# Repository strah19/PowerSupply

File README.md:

# Power Supply

Basic controllable voltage power supply designed for a Eurorack. It includes a positive and negative voltage rail with an AC input.

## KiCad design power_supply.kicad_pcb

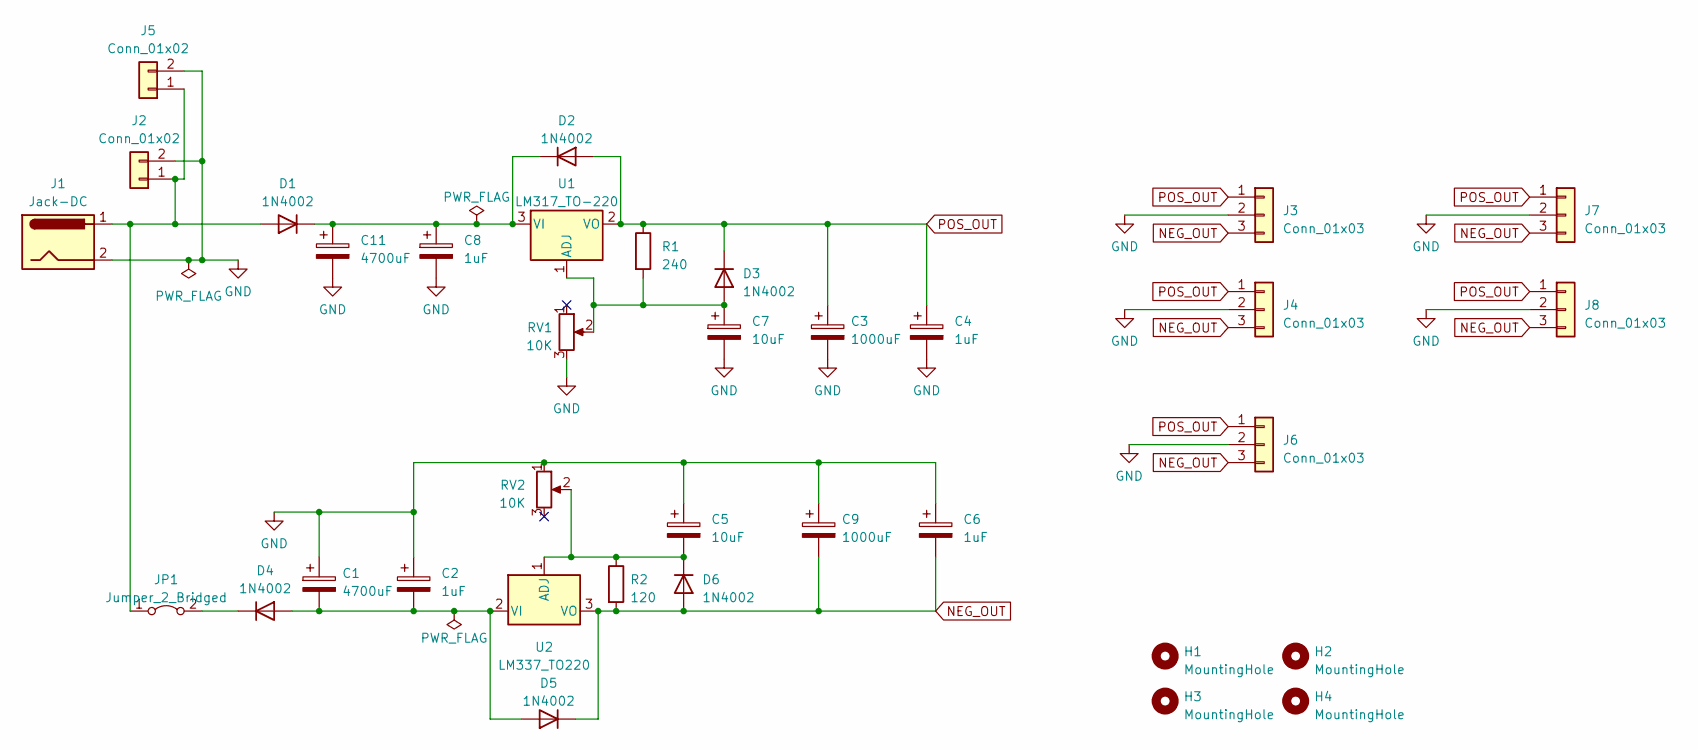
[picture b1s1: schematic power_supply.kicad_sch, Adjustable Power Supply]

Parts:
C1, C11: 4700uF; CP_Radial_D18.0mm_P7.50mm
C2, C4, C6, C8: 1uF; CP_Radial_D5.0mm_P2.50mm
C3, C9: 1000uF; CP_Radial_D13.0mm_P7.50mm
C5, C7: 10uF; CP_Radial_D5.0mm_P2.50mm
D1, D2, D3, D4, D5, D6: 1N4002; D_A-405_P7.62mm_Horizontal
H1, H2, H3, H4: MountingHole; MountingHole_3.2mm_M3_DIN965_Pad
J1: Jack-DC; BarrelJack_Horizontal
J2: Conn_01x02; PinHeader_1x02_P2.54mm_Vertical
J3, J4, J7, J8: Conn_01x03; PinHeader_1x03_P2.54mm_Vertical
J5: Conn_01x02; TerminalBlock_bornier-2_P5.08mm
J6: Conn_01x03; TerminalBlock_bornier-3_P5.08mm
JP1: Jumper_2_Bridged; PinHeader_1x02_P2.54mm_Vertical
R1: 240; R_Axial_DIN0207_L6.3mm_D2.5mm_P10.16mm_Horizontal
R2: 120; R_Axial_DIN0207_L6.3mm_D2.5mm_P10.16mm_Horizontal
RV1, RV2: 10K; Potentiometer_Bourns_3296W_Vertical
U1: LM317_TO-220; TO-220-3_Vertical
U2: LM337_TO220; TO-220-3_Vertical

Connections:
GND: C1.1, C2.1, C3.2, C4.2, C5.1, C6.1, C7.2, C8.2, C9.1, C11.2, J1.2, J2.2, J3.2, J4.2, J5.2, J6.2, J7.2, J8.2, RV1.3, RV2.1
NEG_OUT: C6.2, C9.2, D5.1 (K), D6.2 (A), J3.3, J4.3, J6.3, J7.3, J8.3, R2.2, U2.3 (VO)
unnamed: D1.2 (A), J1.1, J2.1, J5.1, JP1.1 (A)
unnamed: C8.1, C11.1, D1.1 (K), D2.1 (K), U1.3 (VI)
unnamed: C7.1, D3.2 (A), R1.2, RV1.2, U1.1 (ADJ)
unnamed: C1.2, C2.2, D4.2 (A), D5.2 (A), U2.2 (VI)
unnamed: D4.1 (K), JP1.2 (B)
unnamed: C5.2, D6.1 (K), R2.1, RV2.2, U2.1 (ADJ)
POS_OUT: C3.1, C4.1, D2.2 (A), D3.1 (K), J3.1, J4.1, J6.1, J7.1, J8.1, R1.1, U1.2 (VO)

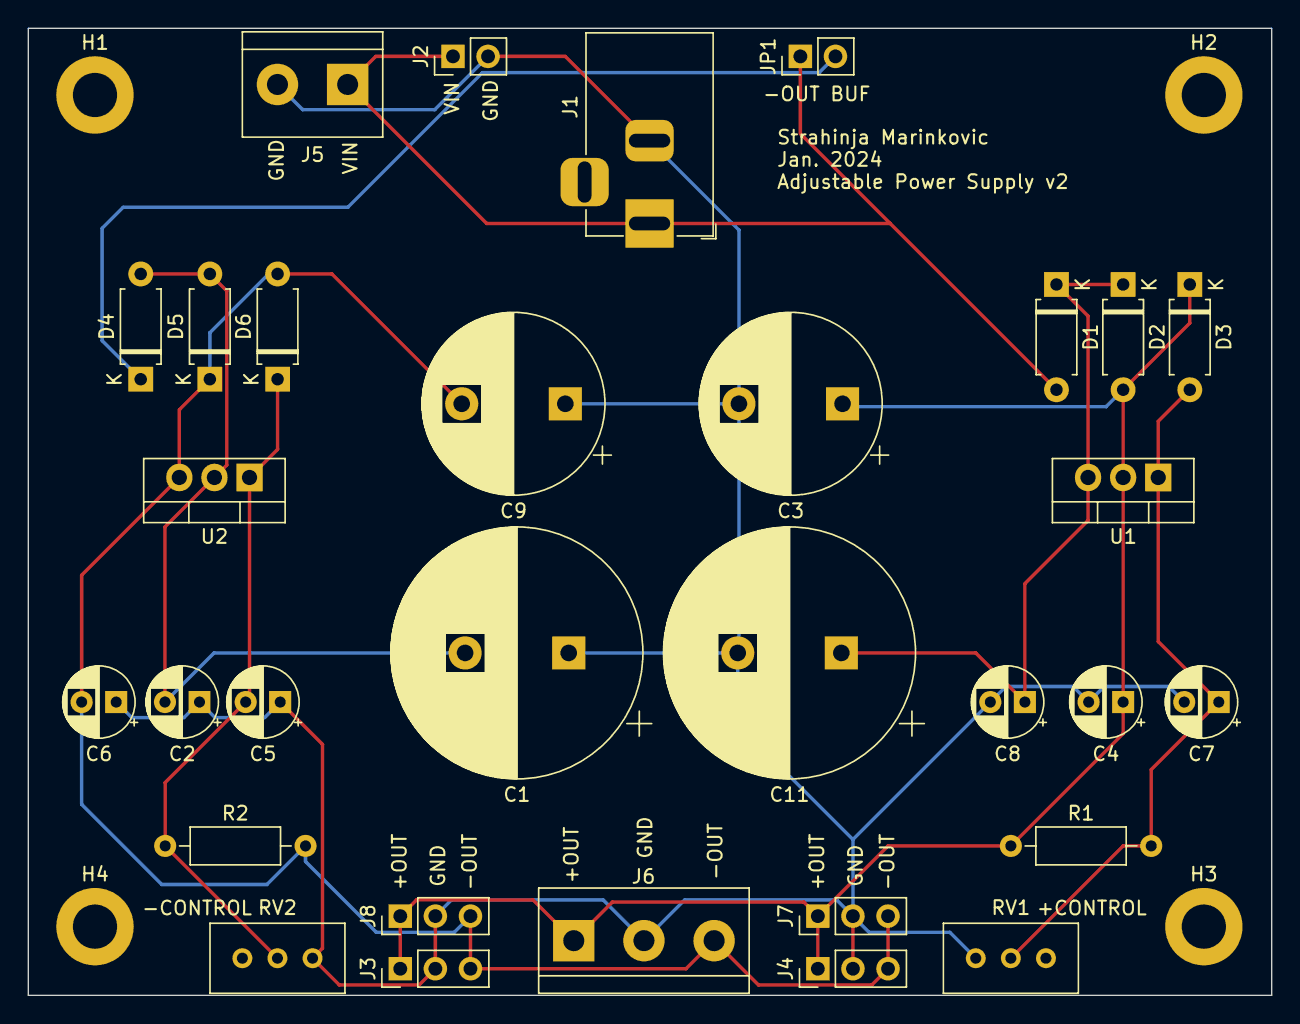
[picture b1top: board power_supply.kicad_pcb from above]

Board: 2 copper layers, 90.0 x 70.0 mm, 35 parts (0 on the bottom side), 9 nets.
